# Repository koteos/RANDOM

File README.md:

# RANDOM
Several Python programs

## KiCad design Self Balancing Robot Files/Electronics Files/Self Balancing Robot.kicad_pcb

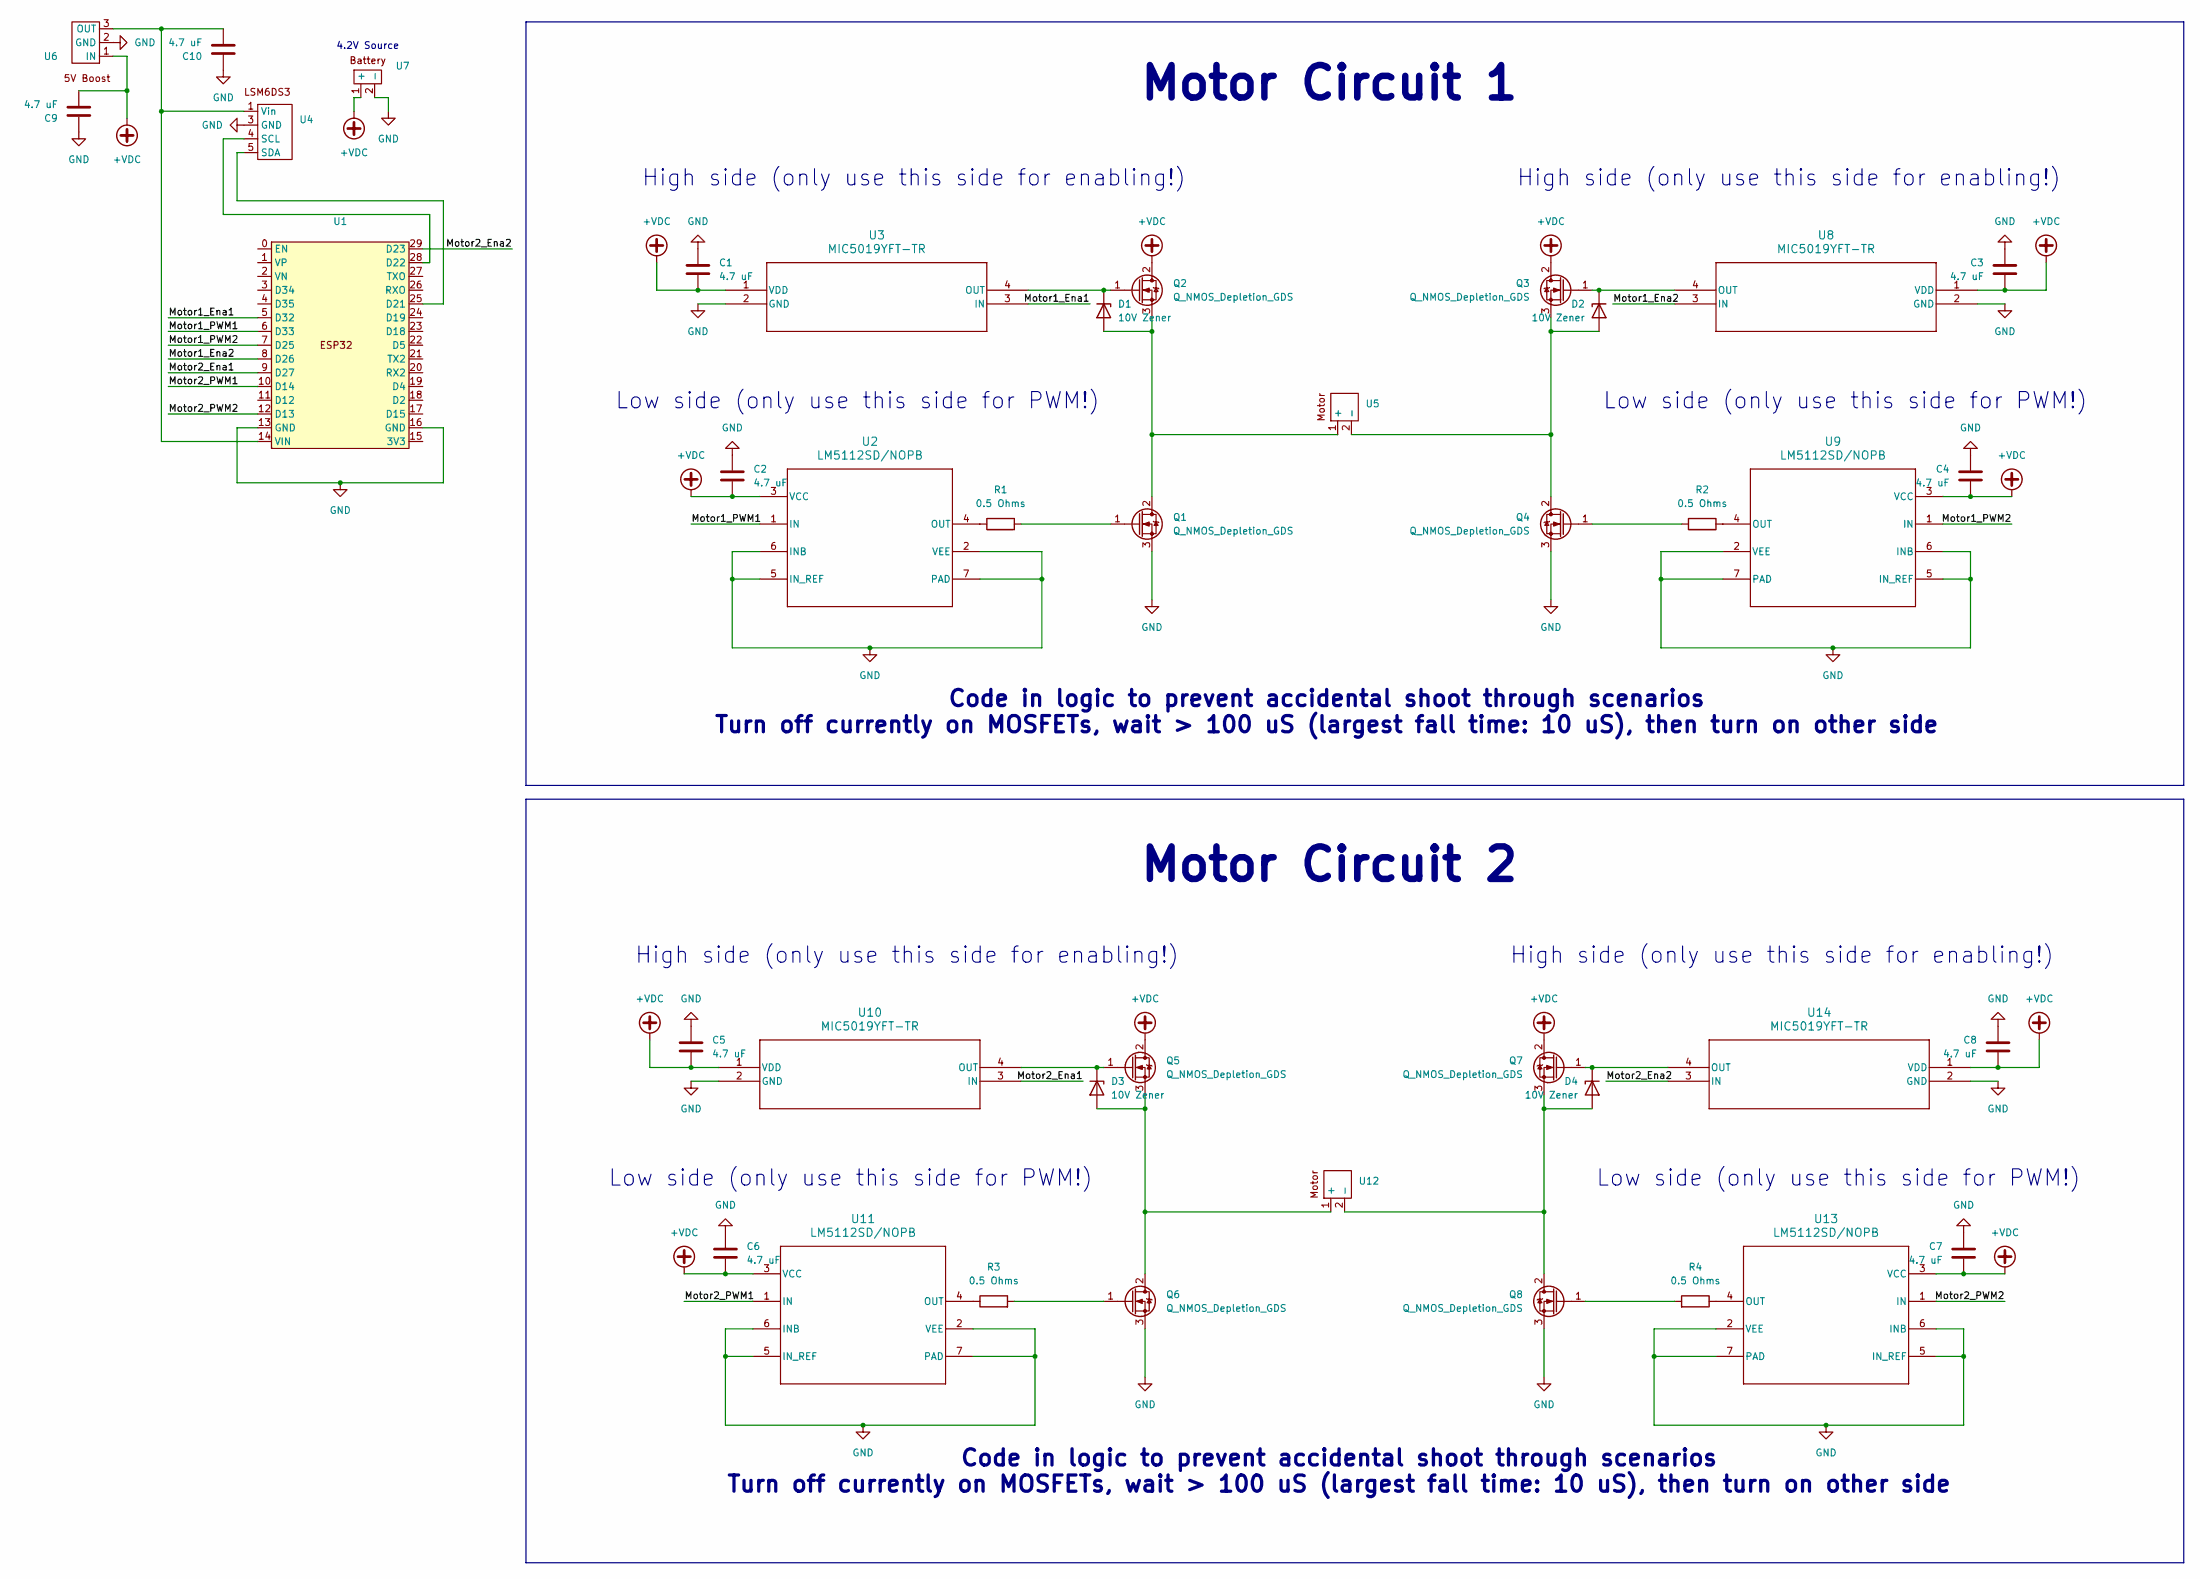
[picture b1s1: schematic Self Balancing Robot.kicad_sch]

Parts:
C1, C2, C3, C4, C5, C6, C7, C8, C9, C10: 4.7 uF; C_0805_2012Metric_Pad1.18x1.45mm_HandSolder
D1, D2, D3, D4: 10V Zener; TSOT-23
Q1, Q2, Q3, Q4, Q5, Q6, Q7, Q8: Q_NMOS_Depletion_GDS; TO-252-2
R1, R2, R3, R4: 0.5 Ohms; R_2010_5025Metric_Pad1.40x2.65mm_HandSolder
U1: ESP32
U2, U9, U11, U13: LM5112SD/NOPB; LM5112SD
U3, U8, U10, U14: MIC5019YFT-TR
U4: LSM6DS3
U5, U12: Motor
U6: Boost
U7: Battery

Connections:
+VDC: C1.2, C2.2, C3.2, C4.2, C5.2, C6.2, C7.2, C8.2, C9.2, Q2.2 (D), Q3.2 (D), Q5.2 (D), Q7.2 (D), U2.3 (VCC), U3.1 (VDD), U6.1 (IN), U7.1 (+), U8.1 (VDD), U9.3 (VCC), U10.1 (VDD), U11.3 (VCC), U13.3 (VCC), U14.1 (VDD)
/Motor1_Ena1: U1.5 (D32), U3.3 (IN)
/Motor1_Ena2: U1.8 (D26), U8.3 (IN)
/Motor1_PWM1: U1.6 (D33), U2.1 (IN)
/Motor1_PWM2: U1.7 (D25), U9.1 (IN)
/Motor2_Ena1: U1.9 (D27), U10.3 (IN)
/Motor2_Ena2: U1.29 (D23), U14.3 (IN)
/Motor2_PWM1: U1.10 (D14), U11.1 (IN)
/Motor2_PWM2: U1.12 (D13), U13.1 (IN)
GND: C1.1, C2.1, C3.1, C4.1, C5.1, C6.1, C7.1, C8.1, C9.1, C10.1, Q1.3 (S), Q4.3 (S), Q6.3 (S), Q8.3 (S), U1.13 (GND), U1.16 (GND), U2.2 (VEE), U2.5 (IN_REF), U2.6 (INB), U2.7 (PAD), U3.2 (GND), U4.3 (GND), U6.2 (GND), U7.2 (-), U8.2 (GND), U9.2 (VEE), U9.5 (IN_REF), U9.6 (INB), U9.7 (PAD), U10.2 (GND), U11.2 (VEE), U11.5 (IN_REF), U11.6 (INB), U11.7 (PAD), U13.2 (VEE), U13.5 (IN_REF), U13.6 (INB), U13.7 (PAD), U14.2 (GND)
unnamed: D1.1 (A), Q1.2 (D), Q2.3 (S), U5.1 (+)
unnamed: D1.3 (K), Q2.1 (G), U3.4 (OUT)
unnamed: D2.1 (A), Q3.3 (S), Q4.2 (D), U5.2 (-)
unnamed: D2.3 (K), Q3.1 (G), U8.4 (OUT)
unnamed: D3.1 (A), Q5.3 (S), Q6.2 (D), U12.1 (+)
unnamed: D3.3 (K), Q5.1 (G), U10.4 (OUT)
unnamed: D4.1 (A), Q7.3 (S), Q8.2 (D), U12.2 (-)
unnamed: D4.3 (K), Q7.1 (G), U14.4 (OUT)
unnamed: Q1.1 (G), R1.2
unnamed: Q4.1 (G), R2.2
unnamed: Q6.1 (G), R3.2
unnamed: Q8.1 (G), R4.2
unnamed: U1.25 (D21), U4.5 (SDA)
unnamed: U1.28 (D22), U4.4 (SCL)
unnamed: C10.2, U1.14 (VIN), U4.1 (Vin), U6.3 (OUT)
unnamed: R1.1, U2.4 (OUT)
unnamed: R2.1, U9.4 (OUT)
unnamed: R3.1, U11.4 (OUT)
unnamed: R4.1, U13.4 (OUT)

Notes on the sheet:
Low side (only use this side for PWM!)
High side (only use this side for enabling!)
Code in logic to prevent accidental shoot through scenarios Turn off currently on MOSFETs, wait > 100 uS (largest fall time: 10 uS), then turn on other side
4.2V Source
Motor Circuit 2
Motor Circuit 1

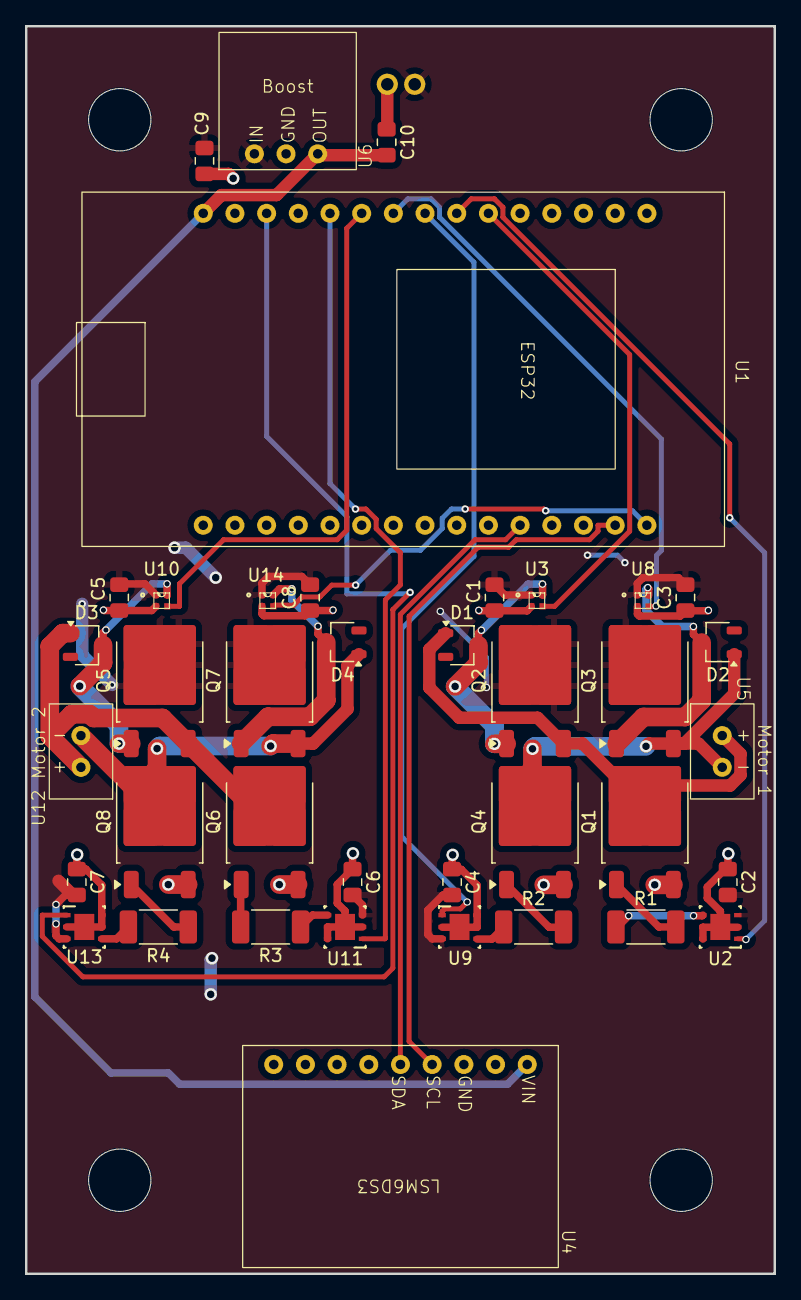
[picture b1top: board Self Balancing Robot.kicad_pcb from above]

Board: 2 copper layers, 60.0 x 100.0 mm, 40 parts (1 on the bottom side), 29 nets.

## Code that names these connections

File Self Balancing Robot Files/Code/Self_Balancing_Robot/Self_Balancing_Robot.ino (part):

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float gyroUncertainty = 4; //Educated guess of the gyroscope angle per second uncertainty

//Motor variables
const int Motor1_Ena1 = 32;
const int Motor1_PWM1 = 33;
const int Motor1_PWM2 = 25;
const int Motor1_Ena2 = 26;
const int Motor2_Ena1 = 27;
const int Motor2_PWM1 = 14;
const int Motor2_PWM2 = 13;
const int Motor2_Ena2 = 23;

//7000*2^12 = 28,672,000 Hz < 40 MHz, so good to go.
const int PWM_Frequency = 7000;
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void setup() {
  
  //Motor setup
  pinMode(Motor1_Ena1, OUTPUT);
  pinMode(Motor1_PWM1, OUTPUT);
  pinMode(Motor1_PWM2, OUTPUT);
  pinMode(Motor1_Ena2, OUTPUT);
  pinMode(Motor2_Ena1, OUTPUT);
  pinMode(Motor2_PWM1, OUTPUT);
  pinMode(Motor2_PWM2, OUTPUT);
  pinMode(Motor2_Ena2, OUTPUT);

  ledcSetup(0, PWM_Frequency, PWM_Resolution);
  ledcSetup(1, PWM_Frequency, PWM_Resolution);
  ledcSetup(2, PWM_Frequency, PWM_Resolution);
  ledcSetup(3, PWM_Frequency, PWM_Resolution);

  ledcAttachPin(Motor1_PWM1, 0);
  ledcAttachPin(Motor1_PWM2, 1);
  ledcAttachPin(Motor2_PWM1, 2);
  ledcAttachPin(Motor2_PWM2, 3);
  
  digitalWrite(Motor1_Ena1, LOW);
  ledcWrite(0, 0); //Motor1_PWM1
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  if (speed < 0)
  {
    digitalWrite(Motor1_Ena1, HIGH);
    ledcWrite(1, constrain(abs(speed), 0, 4095)); //Motor1_PWM2
  }

  if (speed > 0)
  {
    digitalWrite(Motor1_Ena2, HIGH);
    ledcWrite(0, constrain(speed, 0, 4095)); //Motor1_PWM1
  }
  prev_Speed = speed; //save the current speed for next time function is called
}
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  if (speed > 0)
  {
    digitalWrite(Motor2_Ena1, HIGH);
    ledcWrite(3, constrain(speed, 0, 4095)); //Motor2_PWM2
  }

  if (speed < 0)
  {
    digitalWrite(Motor2_Ena2, HIGH);
    ledcWrite(2, constrain(abs(speed), 0, 4095)); //Motor2_PWM1
  }
  prev_Speed = speed; //save the current speed for next time function is called
}
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
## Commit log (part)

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2025-02-13 several code
2025-03-06 Update CLACULADORAS_MENU.py
    Se actualizo la calculadora, ahora cuenta con 2 calculadoras, faltan 2 mas
2025-04-14 Create DSPICC33_FOC_BRUSHLESS
    Test para brushless con un control FOC
2025-04-29 realice algunos cambios
    Varios
2025-05-05 nueva carpeta para control LQR
    Estamos desarrollando el control para la gravedad cero neumatica
2025-05-05 Modificacion de la calculadora
    Agregamos entrada de datos y continuacion de calculos
2025-07-25 Image_clear
    Programa para poner fondo blanco y mejorar fotos
2025-07-25 nuevo archivo
    solo para permitir la carpeta
2025-08-14 Date change
    Date change
2025-08-14 nuevo modelo de negocio Asistentes 2025
2025-09-29 Grafica del resorte
    Para Lexa PI
2026-03-03 nuevas calculadoras
2026-03-09 actualizaciones
2026-03-09 Calculadora actualizada
    tiene calculo de fuerza de cilindro
2026-03-17 LEXA PI
    PANACEA VERSION
2026-03-17 TWO CHANGES
    HOMOLOGATION VERSION
2026-03-18 Cambie la cola
    Se modifica la cola porque senti contacto con mi espalda, aun no se fabrica y prueba
2026-03-21 VERSION 3
    VERSION QUE TAMBIEN CALIFICA EN LA TABLA
2026-03-21 LEXA WS
    PROYECTO ACTUALIZADO AL ULTIMO ESTADO
2026-03-27 BRAZO HEINEKEN
2026-03-27 GRIPPER
2026-03-27 gravedad cero
2026-03-27 actualizacion junta
2026-03-28 Revision Heieneken
2026-03-29 mejoras
2026-03-29 avance
2026-03-30 actualizacion
2026-03-31 DAY UPDATE
2026-04-01 7.14 update
2026-04-07 update 060426
    Modificacionde piezas para que pueda abrir y cerrar el antebrazo
2026-04-08 uodate exo 080426
2026-04-10 UPDATE HEINEKEN
2026-04-10 update_100426
2026-04-13 update 130426
    modifique dimensiones
2026-04-13 COPIA ANTEBRAZO
2026-04-15 Exo_Legs
2026-04-16 emcanismo bote
2026-04-20 VERSION 1.7 SHEET_METAL
    Deje la version de lamina doblada en 1.7 para seguir trabajando 1.6 para fabricar en china
2026-04-23 Lexa y AwareTrack
2026-04-24 updatr
2026-04-27 UPDATE
    FINISH 1
2026-04-27 update
    coloque barrenos para una base
2026-04-30 NUIEVA VERSION 1.8
    Se agrega nueva version para trabajar un modelo comrecial ligero y pasivo
2026-04-30 daba problemas de sincronizacio
    esta respaldado en escritorio de multivac
2026-05-03 UODATE
    base privisional montaje
2026-05-13 Soporte nuevo
    Diseño de nuevo soporte para canal U
2026-06-07 ERGOEVAL
